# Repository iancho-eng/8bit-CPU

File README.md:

# 🖥️ 8-Bit CPU — Discrete Logic Computer

A fully functional 8-bit CPU designed in KiCAD and prototyped on breadboards, built from discrete TTL (74LS series) logic ICs with a microcoded control unit stored in parallel EEPROMs. The full design has now been carried from schematics through to custom, routed PCBs for every module.

> Inspired by Ben Eater's 8-bit computer series, this implementation extends the original design with custom modifications in components, organization, and debugging instrumentation.

---

## 📸 Overview

The processor implements a classic **von Neumann architecture** with a shared 8-bit data bus, fetch–decode–execute pipeline, and over **80 LEDs** for real-time visualization of control signals, bus traffic, and register contents.

---

## ✨ Features

- **Adjustable clock**: sub-Hz manual stepping up to ~100 kHz continuous operation
- **Manual single-step mode**: debounced pushbutton for step-through debugging
- **Microcoded control unit**: EEPROM-based microcode with up to 8 micro-steps per instruction
- **Rich LED instrumentation**: >80 LEDs tracing every register, bus line, and control signal
- **7-segment display output**: binary-to-decimal decoding via EEPROM lookup table
- **Signed/unsigned display modes**: selectable via mode control input
- **Program Mode / Run Mode**: front-panel DIP switches for manual memory programming

---

## 🏗️ Architecture

```
┌─────────────────────────────────────────────┐
│              Control Logic                  │
│           (EEPROM + Step Counter)           │
└────────────────────┬────────────────────────┘
                     │
              ┌──────▼───────┐
              │   8-bit BUS  │
              └──────┬───────┘
       ┌─────────────┼─────────────┐
       │             │             │
  ┌────▼────┐  ┌─────▼─────┐ ┌────▼────┐
  │   PC    │  │  Registers │ │   ALU   │
  │(HCT161) │  │ A / B / IR │ │(LS283×2)│
  └────┬────┘  └─────┬─────┘ └────┬────┘
       │             │             │
  ┌────▼────┐  ┌─────▼─────┐ ┌────▼────┐
  │   MAR   │  │    RAM     │ │ Output  │
  │         │  │ (74189 ×2) │ │Register │
  └─────────┘  └───────────┘ └─────────┘
```

### System Characteristics

| Property       | Value                                    |
| -------------- | ----------------------------------------- |
| Bus Width      | 8-bit shared data bus                    |
| Clock Speed    | Sub-Hz (manual) to ~100 kHz (continuous) |
| Supply Voltage | 5V DC regulated                          |
| RAM            | 128 bytes (74189 × 2)                    |
| Indicators     | >80 LEDs                                 |
| Logic Family   | TTL — 74LS / 74HCT series                |
| PCB Stack-up   | 2-layer (F.Cu / B.Cu), KiCad              |

---

## 🔩 PCB Design

Every module of the CPU has been fully migrated from breadboard schematic to a routed, 2-layer KiCad PCB. Each board is a standalone module that plugs into the shared 8-bit bus, keeping the system modular and easy to debug or re-spin individually.

### Register A

8-bit accumulator register (`pcb/Register_A/Register_A.kicad_pcb`) — dual 74HCT173 D-type registers cascaded for 8 bits, bus-isolated via 74HCT245 transceiver, with LED taps on every output bit.

### Register B

8-bit operand register (`pcb/Register_B/Register_B.kicad_pcb`) — same 74HCT173 + 74HCT245 architecture as Register A.

### ALU

Dual 74LS283 4-bit adders (`pcb/ALU/ALU.kicad_pcb`) cascaded for 8-bit arithmetic, with a 74LS86 XOR network for two's-complement subtraction and 74LS02/74LS08 gating for the carry/zero flag logic.

### RAM

128-byte static RAM (`pcb/RAM/RAM.kicad_pcb`) — dual 74189 RAM chips, 74LS157 address/data muxing, 74LS04 inversion correction, and an 8-position DIP switch bank for manual Program Mode entry.

### MAR + Instruction Register

Memory Address Register and Instruction Register combined on one board (`pcb/MAR_Instruction_Register/MAR_Instruction_Register.kicad_pcb`) — dual 74HCT173 registers with manual DIP-switch address entry; the IR splits into opcode (upper nibble, to control logic) and operand (lower nibble, to bus).

### Program Counter + Output Register

Combined PC and display output board (`pcb/Program_Counter_Output_Register/Program_Counter_Output_Register.kicad_pcb`) — 74HCT161 program counter, 74HCT273 output latch, EEPROM-based binary-to-7-segment lookup table, and 74LS76/74LS08 digit-multiplexing driving a 4-digit CA56-12CGWA display.

### Control Logic

Microcode sequencer (`pcb/Control_Logic/Control_Logic.kicad_pcb`) — dual 28C16 EEPROMs storing `(opcode + step + flags) → control signals`, a 74HCT161 step counter, and LED taps on every control line.

### Clock

Clock generator (`pcb/Clock/Clock.kicad_pcb`) — triple 555 timer setup (astable for continuous clocking, monostable for debounced single-step), trimmer-potentiometer frequency control, and a run/step mode switch.

---

## 🔧 Modules

### Clock Module

- 555 timer in **astable mode** for continuous operation
- Potentiometer-controlled frequency (sub-Hz to ~100 kHz)
- Debounced pushbutton (555 in monostable mode) for single-step debugging

### Register Modules (A, B, Instruction)

- Built from **74HCT173** 4-bit D-type registers (cascaded pairs for 8-bit)
- All registers bus-isolated via **74LS245** transceivers
- LED taps on all outputs for real-time binary visualization
- IR splits into **opcode (upper nibble)** → control logic and **operand (lower nibble)** → bus

### ALU

- Dual **74LS283** 4-bit adders cascaded for 8-bit arithmetic
- XOR gate network (74LS86) enables **two's complement subtraction** via SUB control line
- Supports: `ADD`, `SUB`, bitwise `AND` / `OR` / `NOT` / `XOR`
- **Carry Flag (CF)**: MSB carry-out
- **Zero Flag (ZF)**: NOR/AND gate detection of all-zero result

### RAM

- Two **74189** static RAMs → 128 bytes total
- **Program Mode**: DIP switches + debounced write button
- **Run Mode**: CPU owns the bus; DIP inputs ignored
- 74LS157 multiplexers handle address/data source selection
- Data inversion corrected with 74LS04 inverters

### Program Counter (PC)

- **74HCT161** 4-bit synchronous counter + **74HCT245** bus transceiver
- Control inputs: `Load` (jump), `Enable` (controlled increment), `Clear/Reset`
- Green LEDs on output lines for address visualization

### Output Module

- **74HC273** octal D-type latch captures 8-bit bus value
- **28C16 EEPROM** as binary-to-7-segment lookup table
- **555 timer** + 74LS76 JK flip-flops + 74ACT139 decoder for digit multiplexing
- **CA56-12CGWA** 4-digit 7-segment display array
- Supports signed and unsigned decimal display modes

### Control Logic

- Two **28C16 EEPROMs** store microcode: `(opcode + step + flags) → control signals`
- **74HCT161** step counter cycles through up to 8 micro-steps per instruction
- Zero and Carry flags feed back into EEPROM address lines for conditional branching (`JZ`, `JC`)
- All control lines LED-tapped for real-time instruction sequencing visibility

---

## 📋 Instruction Set

| Mnemonic | Operation                    |
| -------- | ----------------------------- |
| `LDA`    | Load A register from memory  |
| `STA`    | Store A register to memory   |
| `ADD`    | Add memory value to A        |
| `SUB`    | Subtract memory value from A |
| `JMP`    | Unconditional jump           |
| `JC`     | Jump if carry flag set       |
| `JZ`     | Jump if zero flag set        |
| `OUT`    | Output A register to display |
| `HLT`    | Halt execution               |

---

## 💾 Sample Program

```
LDA 14    ; Load value at address 14 into register A
ADD 15    ; Add value at address 15 to register A
OUT       ; Latch result to 7-segment display
HLT       ; Halt
```

**Expected behavior**: fetches two operands from addresses 14 and 15, sums them in the ALU, and displays the decimal result on the 7-segment display before halting.

---

## 🛠️ Tools & Resources

| Tool                   | Purpose                                                           |
| ----------------------- | ------------------------------------------------------------------ |
| **KiCAD**               | Schematic design & PCB layout                                     |
| **Arduino IDE**         | EEPROM programmer firmware                                        |
| **Arduino Nano**        | Custom EEPROM programmer (with shift registers)                   |
| **LucidChart**          | Block diagram representation                                      |
| **Ben Eater's Series**  | Architecture reference — [eater.net/8bit](https://eater.net/8bit) |

---

## ⚙️ Operating Instructions

1. Connect a regulated **5V DC** supply to the PCB stack
2. Set the mode switch to **Program Mode**
3. Use DIP switches to set address and data values; press **WRITE** to store each byte
4. Switch to **Run Mode**
5. Select **Manual** (single-step) or **Continuous** clock mode
6. Press **RESET** to clear the PC and registers
7. Start the clock and observe execution on LEDs and 7-segment displays

---

## ⚠️ Limitations

- **Memory**: 128 bytes total RAM
- **Speed**: ~100 kHz practical limit (bounded by 74LS propagation delays and board wiring)
- **Debugging**: Longer programs require careful micro-step tracing
- **EEPROM wear**: 28C16 devices have finite write cycles — re-flash microcode judiciously

---

## 🚧 Current Status

- [x] Breadboard prototype functional
- [x] All modules designed in KiCAD
- [x] Arduino Nano EEPROM programmer built and tested
- [x] Decoupling/bypass capacitors added throughout
- [x] PCB layout routing complete for all 8 modules
- [x] PCB prototype fabrication & testing
- [ ] Full-system bring-up on fabricated boards

---

## 📄 License

This project is open-source and available under the [MIT License](https://github.com/iancho-eng/8bit-CPU/blob/main/LICENSE).

---

## 🙏 Acknowledgements

This project draws heavy inspiration from **Ben Eater's 8-bit computer series**. His tutorials and schematics provided a foundational understanding of CPU architecture. This implementation adapts and extends the design with independent modifications, additional debugging instrumentation, and a complete migration from breadboard to custom PCBs.

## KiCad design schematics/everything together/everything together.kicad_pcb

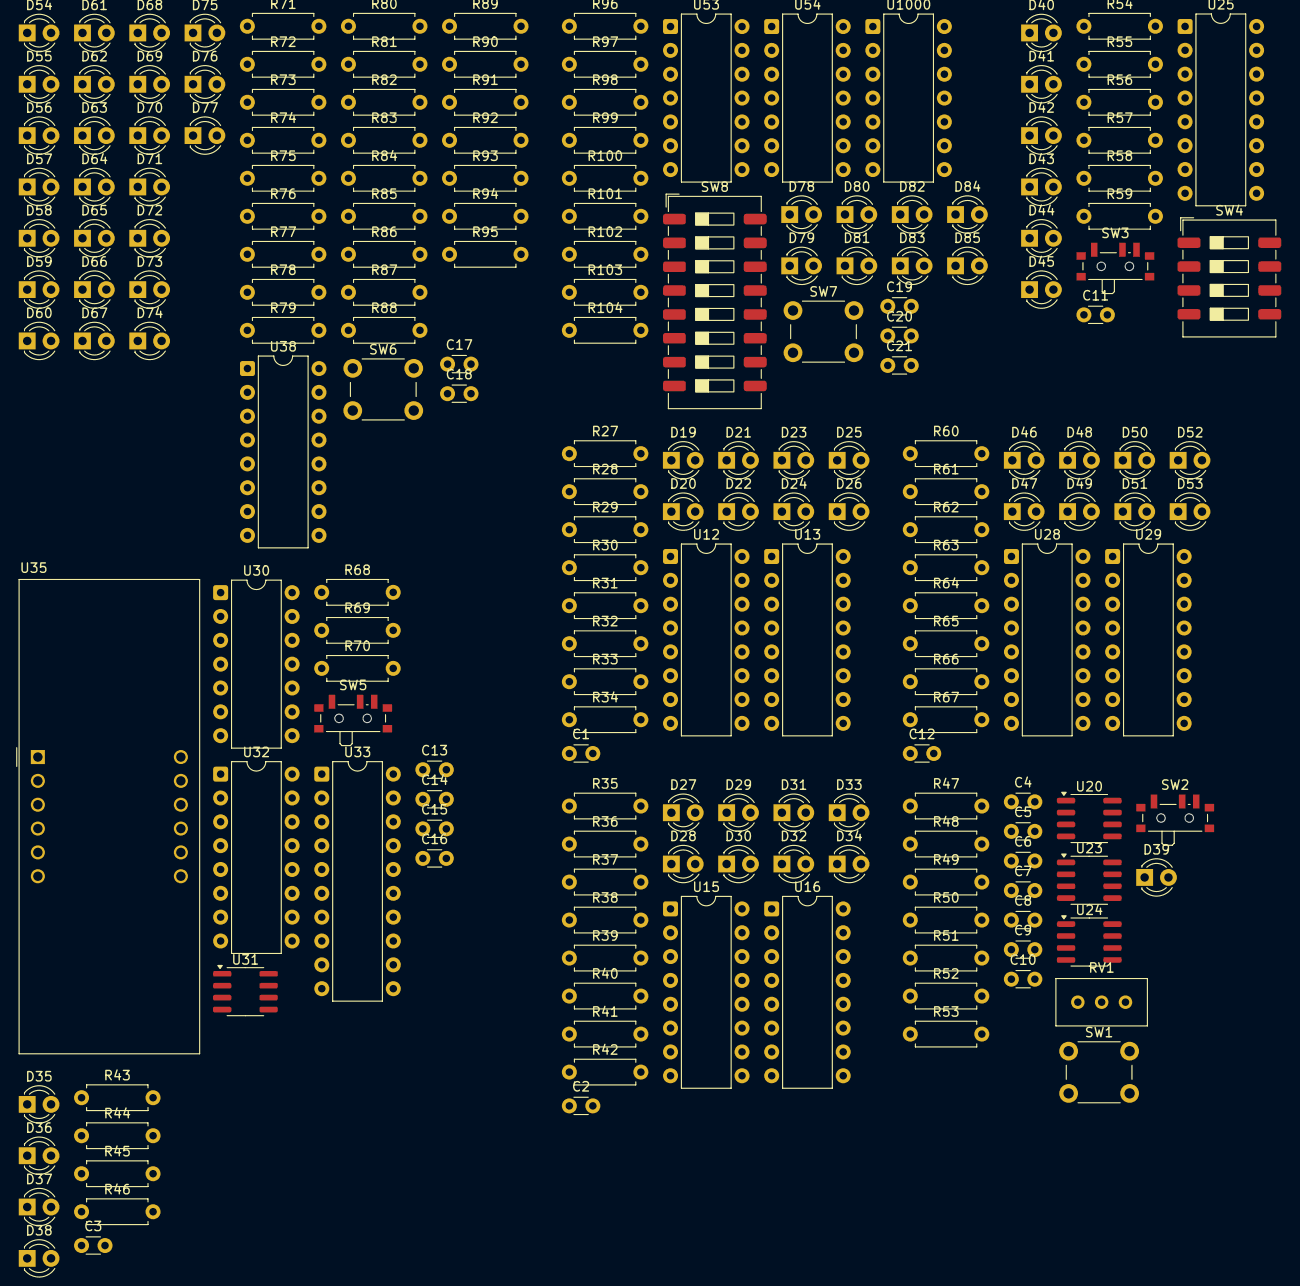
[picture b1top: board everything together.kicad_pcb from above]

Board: 2 copper layers, 194 parts (0 on the bottom side), 146 nets, no tracks yet.

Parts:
C1, C2, C3, C5, C9, C10, C12, C15, C16, C17, C18, C20, C21: 0.1uF; C_Disc_D3.0mm_W1.6mm_P2.50mm
C4, C6, C8, C13, C14, C19: 0.01uF; C_Disc_D3.0mm_W1.6mm_P2.50mm
C7: 1uF; C_Disc_D3.0mm_W1.6mm_P2.50mm
C11: C; C_Disc_D3.0mm_W1.6mm_P2.50mm
D19, D20, D21, D22, D23, D24, D25, D26, D27, D28, D29, D30, D31, D32, D33, D34, D41, D59, D60, D61, D78, D79, D80, D81, D82, D83, D84, D85: RED; LED_D3.0mm
D35, D36, D37, D38, D40, D54, D55, D56, D57, D58: GREEN; LED_D3.0mm
D39, D46, D47, D48, D49, D62, D63, D64, D65, D66, D67, D68, D69, D70, D71, D72, D73, D74, D75, D76, D77: BLUE; LED_D3.0mm
D42, D43, D44, D45, D50, D51, D52, D53: YELLOW; LED_D3.0mm
R27, R28, R29, R30, R31, R32, R33, R34, R35, R36, R37, R38, R39, R40, R41, R42, R43, R44, R45, R46, R51, R56, R57, R58, R59, R60, R61, R62, R63, R64, R65, R66, R67, R71, R72, R73, R74, R75, R77, R78, R79, R80, R81, R82, R83, R84, R85, R86, R87, R88, R89, R90, R91, R92, R93, R94, R95, R96, R97, R98, R99, R100, R101, R102, R103: 220; R_Axial_DIN0207_L6.3mm_D2.5mm_P7.62mm_Horizontal
R47, R49, R50, R52, R53, R54, R55, R76, R104: 1K; R_Axial_DIN0207_L6.3mm_D2.5mm_P7.62mm_Horizontal
R48: 1M; R_Axial_DIN0207_L6.3mm_D2.5mm_P7.62mm_Horizontal
R68: 10k; R_Axial_DIN0207_L6.3mm_D2.5mm_P7.62mm_Horizontal
R69: 100k; R_Axial_DIN0207_L6.3mm_D2.5mm_P7.62mm_Horizontal
R70: 1k; R_Axial_DIN0207_L6.3mm_D2.5mm_P7.62mm_Horizontal
RV1: 1M; Potentiometer_Bourns_3296W_Vertical
SW1, SW6, SW7: SW_Push; SW_PUSH_6mm
SW2, SW3, SW5: SW_SPDT; SW_SPDT_PCM12
SW4: SW_DIP_x04; SW_DIP_SPSTx04_Slide_9.78x12.34mm_W8.61mm_P2.54mm
SW8: SW_DIP_x08; SW_DIP_SPSTx08_Slide_9.78x22.5mm_W8.61mm_P2.54mm
U12, U13, U15, U16, U25, U28, U29: 74HCT173; DIP-16_W7.62mm
U20, U23, U24, U31: LM555xM; SOIC-8_3.9x4.9mm_P1.27mm
U30: 74LS08; DIP-14_W7.62mm
U32: 74LS76; DIP-16_W7.62mm
U33: 74HCT273; DIP-20_W7.62mm
U35: CA56-12CGKWA
U38: 74HCT138; DIP-16_W7.62mm
U53, U1000: 74HCT04; DIP-14_W7.62mm
U54: 7400; DIP-14_W7.62mm

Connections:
/ALU/A_0: D26.2 (A), U13.6 (Q3)
/ALU/A_1: D25.2 (A), U13.5 (Q2)
/ALU/A_2: D24.2 (A), U13.4 (Q1)
/ALU/A_3: D23.2 (A), U13.3 (Q0)
/ALU/A_4: D22.2 (A), U12.6 (Q3)
/ALU/A_5: D21.2 (A), U12.5 (Q2)
/ALU/A_6: D20.2 (A), U12.4 (Q1)
/ALU/A_7: D19.2 (A), U12.3 (Q0)
/ALU/BUS_0: U13.11 (D3), U16.11 (D3), U25.11 (D3), U29.11 (D3), U33.3 (D0)
/ALU/BUS_1: U13.12 (D2), U16.12 (D2), U25.12 (D2), U29.12 (D2), U33.4 (D1)
/ALU/BUS_2: U13.13 (D1), U16.13 (D1), U25.13 (D1), U29.13 (D1), U33.7 (D2)
/ALU/BUS_3: U13.14 (D0), U16.14 (D0), U25.14 (D0), U29.14 (D0), U33.8 (D3)
/ALU/BUS_4: U12.11 (D3), U15.11 (D3), U28.11 (D3), U33.13 (D4)
/ALU/BUS_5: U12.12 (D2), U15.12 (D2), U28.12 (D2), U33.14 (D5)
/ALU/BUS_6: U12.13 (D1), U15.13 (D1), U28.13 (D1), U33.17 (D6)
/ALU/BUS_7: U12.14 (D0), U15.14 (D0), U28.14 (D0), U33.18 (D7)
/ALU/B_0: D34.2 (A), U16.6 (Q3)
/ALU/B_1: D33.2 (A), U16.5 (Q2)
/ALU/B_2: D32.2 (A), U16.4 (Q1)
/ALU/B_3: D31.2 (A), U16.3 (Q0)
/ALU/B_4: D30.2 (A), U15.6 (Q3)
/ALU/B_5: D29.2 (A), U15.5 (Q2)
/ALU/B_6: D28.2 (A), U15.4 (Q1)
/ALU/B_7: D27.2 (A), U15.3 (Q0)
/ALU/CLK: C19.1, D39.2 (A), U12.7 (Cp), U13.7 (Cp), U15.7 (Cp), U16.7 (Cp), U25.7 (Cp), U28.7 (Cp), U29.7 (Cp), U30.2
/ALU/CLR: U12.15 (Mr), U13.15 (Mr), U15.15 (Mr), U16.15 (Mr), U25.15 (Mr), U28.15 (Mr), U29.15 (Mr)
/Control Logic/IR_4: D49.2 (A), U28.6 (Q3)
/Control Logic/IR_5: D48.2 (A), U28.5 (Q2)
/Control Logic/IR_6: D47.2 (A), U28.4 (Q1)
/Control Logic/IR_7: D46.2 (A), U28.3 (Q0)
/Control Logic/OI: D73.2 (A), U30.1
/Control Logic/RI: D64.2 (A), U54.1
/Control Logic/~AI: U12.9 (E1), U12.10 (E2), U13.9 (E1), U13.10 (E2)
/Control Logic/~BI: U15.9 (E1), U15.10 (E2), U16.9 (E1), U16.10 (E2)
/Control Logic/~II: U28.9 (E1), U28.10 (E2), U29.9 (E1), U29.10 (E2)
/Control Logic/~MI: U25.9 (E1), U25.10 (E2)
/Memory Address Register/Prog: D41.1 (K), SW3.1 (A)
GND: C1.2, C2.2, C3.2, C4.2, C5.2, C6.2, C7.2, C8.2, C9.2, C10.2, C11.2, C12.2, C13.2, C14.2, C15.2, C16.2, C17.2, C18.2, C20.2, C21.2, D59.1 (K), D60.1 (K), D61.1 (K), R27.2, R28.2, R29.2, R30.2, R31.2, R32.2, R33.2, R34.2, R35.2, R36.2, R37.2, R38.2, R39.2, R40.2, R41.2, R42.2, R43.1, R44.1, R45.1, R46.1, R51.2, R56.1, R57.1, R58.1, R59.1, R60.2, R61.2, R62.2, R63.2, R64.2, R65.2, R66.2, R67.2, R68.2, R76.2, R80.2, R81.2, R82.2, R83.2, R84.2, R85.2, R86.2, R87.2, R88.2, R89.2, R90.2, R91.2, R92.2, R93.2, R94.2, R95.2, R96.2, R97.2, R98.2, R99.2, R100.2, R101.2, R102.2, R103.2, R104.2, SW1.1, SW2.2 (B), SW3.2 (B), SW4.3, SW4.4, SW4.7, SW4.8, SW7.2, SW8.3, SW8.4, SW8.7, SW8.8, SW8.11, SW8.12, SW8.15, SW8.16, U12.1 (Oe1), U12.2 (Oe2), U12.8 (GND), U13.1 (Oe1), U13.2 (Oe2), U13.8 (GND), U15.1 (Oe1), U15.2 (Oe2), U15.8 (GND), U16.1 (Oe1), U16.2 (Oe2), U16.8 (GND), U20.1 (GND), U23.1 (GND), U24.1 (GND), U24.6 (THR), U25.1 (Oe1), U25.2 (Oe2), U25.8 (GND), U28.1 (Oe1), U28.2 (Oe2), U28.8 (GND), U29.1 (Oe1), U29.2 (Oe2), U29.8 (GND), U30.7 (GND), U31.1 (GND), U32.13 (GND), U33.10 (GND), U38.4 (~E0), U38.8 (GND), U53.7 (GND), U54.7 (GND), U1000.7 (GND)
unnamed: C19.2, R104.1, U54.2
unnamed: D19.1 (K), R27.1
unnamed: D20.1 (K), R28.1
unnamed: D21.1 (K), R29.1
unnamed: D22.1 (K), R30.1
unnamed: D23.1 (K), R31.1
unnamed: D24.1 (K), R32.1
unnamed: D25.1 (K), R33.1
unnamed: D26.1 (K), R34.1
unnamed: D27.1 (K), R35.1
unnamed: D28.1 (K), R36.1
unnamed: D29.1 (K), R37.1
unnamed: D30.1 (K), R38.1
unnamed: D31.1 (K), R39.1
unnamed: D32.1 (K), R40.1
unnamed: D33.1 (K), R41.1
unnamed: D34.1 (K), R42.1
unnamed: D35.1 (K), R43.2
unnamed: D36.1 (K), R44.2
unnamed: D37.1 (K), R45.2
unnamed: D38.1 (K), R46.2
unnamed: D39.1 (K), R51.1
unnamed: D40.2 (A), R54.2
unnamed: D40.1 (K), SW3.3 (C)
unnamed: D41.2 (A), R55.2
unnamed: D42.1 (K), R56.2
unnamed: D43.1 (K), R57.2
unnamed: D44.1 (K), R58.2
unnamed: D45.1 (K), R59.2
unnamed: D46.1 (K), R60.1
unnamed: D47.1 (K), R61.1
unnamed: D48.1 (K), R62.1
unnamed: D49.1 (K), R63.1
unnamed: D50.2 (A), U29.3 (Q0)
unnamed: D50.1 (K), R64.1
unnamed: D51.2 (A), U29.4 (Q1)
unnamed: D51.1 (K), R65.1
unnamed: D52.2 (A), U29.5 (Q2)
unnamed: D52.1 (K), R66.1
unnamed: D53.2 (A), U29.6 (Q3)
unnamed: D53.1 (K), R67.1
unnamed: D54.2 (A), R71.1
unnamed: D54.1 (K), U38.11 (~Y4)
unnamed: D55.2 (A), R72.1
unnamed: D55.1 (K), U38.12 (~Y3)
unnamed: D56.2 (A), R73.1
unnamed: D56.1 (K), U38.13 (~Y2)
unnamed: D57.2 (A), R74.1
unnamed: D57.1 (K), U38.14 (~Y1)
unnamed: D58.2 (A), R75.1
unnamed: D58.1 (K), U38.15 (~Y0)
unnamed: D59.2 (A), R77.1
unnamed: D60.2 (A), R78.1
unnamed: D61.2 (A), R79.1
unnamed: D62.1 (K), R80.1
unnamed: D63.1 (K), R81.1
unnamed: D64.1 (K), R82.1
unnamed: D65.1 (K), R83.1
unnamed: D66.1 (K), R84.1
unnamed: D67.1 (K), R85.1
unnamed: D68.1 (K), R86.1
unnamed: D69.1 (K), R87.1
unnamed: D70.1 (K), R88.1
unnamed: D71.1 (K), R89.1
unnamed: D72.1 (K), R90.1
unnamed: D73.1 (K), R91.1
unnamed: D74.1 (K), R92.1
unnamed: D75.1 (K), R93.1
unnamed: D76.1 (K), R94.1
unnamed: D77.1 (K), R95.1
unnamed: D78.2 (A), U53.2
unnamed: D78.1 (K), R96.1
unnamed: D79.2 (A), U53.4
unnamed: D79.1 (K), R97.1
unnamed: D80.2 (A), U53.6
unnamed: D80.1 (K), R98.1
unnamed: D81.2 (A), U53.8
unnamed: D81.1 (K), R99.1
unnamed: D82.2 (A), U53.10
unnamed: D82.1 (K), R100.1
unnamed: D83.2 (A), U53.12
unnamed: D83.1 (K), R101.1
unnamed: D84.2 (A), U1000.2
unnamed: D84.1 (K), R102.1
unnamed: D85.2 (A), U1000.4
unnamed: D85.1 (K), R103.1
unnamed: U32.1 (C), U32.10 (~Q)
unnamed: R79.2, U38.1 (A0)
unnamed: R78.2, U38.2 (A1)
unnamed: R77.2, U38.3 (A2)
unnamed: R50.1, RV1.2
unnamed: R76.1, SW6.2
unnamed: R52.2, SW2.1 (A), U24.2 (TR)
unnamed: R53.2, SW2.3 (C), U24.4 (R)
unnamed: R68.1, SW5.1 (A)
unnamed: C4.1, U20.5 (CV)
unnamed: C5.1, R48.2, U20.6 (THR), U20.7 (DIS)
unnamed: R47.2, SW1.2, U20.2 (TR)
unnamed: C6.1, U23.5 (CV)
unnamed: R49.2, R50.2, U23.7 (DIS)
unnamed: C7.1, RV1.3, U23.2 (TR), U23.6 (THR)
unnamed: C8.1, U24.5 (CV)
unnamed: C14.1, U31.5 (CV)
unnamed: R69.1, R70.2, U31.7 (DIS)
unnamed: U31.3 (Q), U32.6 (C)
unnamed: C13.1, R69.2, U31.2 (TR), U31.6 (THR)
unnamed: U30.3, U33.11 (Cp)
VCC: C1.1, C2.1, C3.1, C9.1, C10.1, C11.1, C12.1, C15.1, C16.1, C17.1, C18.1, C20.1, C21.1, R47.1, R48.1, R49.1, R52.1, R53.1, R54.1, R55.1, R70.1, R71.2, R72.2, R73.2, R74.2, R75.2, SW5.3 (C), SW6.1, U12.16 (VCC), U13.16 (VCC), U15.16 (VCC), U16.16 (VCC), U20.4 (R), U20.8 (VCC), U23.4 (R), U23.8 (VCC), U24.8 (VCC), U25.16 (VCC), U28.16 (VCC), U29.16 (VCC), U30.14 (VCC), U31.8 (VCC), U32.2 (~S), U32.3 (~R), U32.4 (J), U32.5 (VCC), U32.7 (~S), U32.8 (~R), U32.9 (J), U32.12 (K), U32.16 (K), U33.20 (VCC), U38.5 (~E1), U38.6 (E2), U38.16 (VCC), U53.14 (VCC), U54.14 (VCC), U1000.14 (VCC)

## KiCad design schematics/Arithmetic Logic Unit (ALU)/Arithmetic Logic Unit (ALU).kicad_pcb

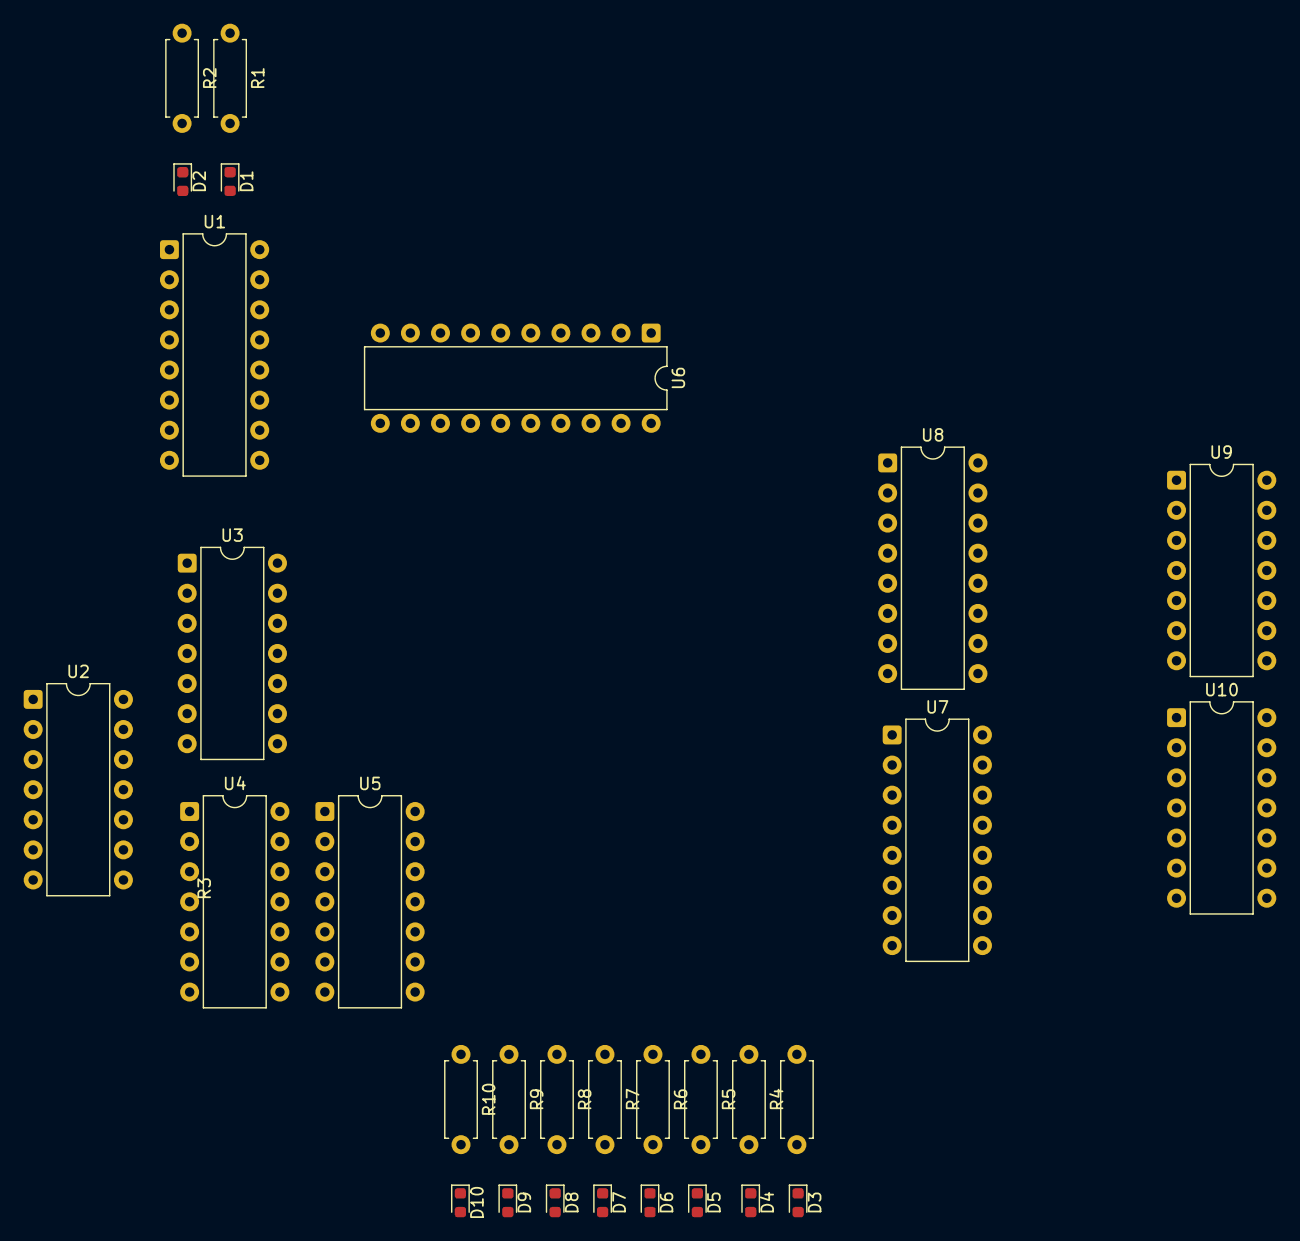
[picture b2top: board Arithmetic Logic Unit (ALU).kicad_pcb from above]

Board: 2 copper layers, 30 parts (0 on the bottom side), 41 nets, no tracks yet.

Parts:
D1, D2, D3, D4, D5, D6, D7, D8, D9, D10: RED; LED_0603_1608Metric
R1, R2, R3, R4, R5, R6, R7, R8, R9, R10: 220; R_Axial_DIN0207_L6.3mm_D2.5mm_P7.62mm_Horizontal
U1: 74HCT173; DIP-16_W7.62mm
U2, U3, U4: 74LS08; DIP-14_W7.62mm
U5: 74LS02; DIP-14_W7.62mm
U6: 74HCT245N; DIP-20_W7.62mm
U7, U8: 74LS283; DIP-16_W7.62mm
U9, U10: 74LS86; DIP-14_W7.62mm

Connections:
/CF: D1.2 (A), U1.3 (Q0)
/SU: U8.7 (C0), U9.1, U9.4, U9.9, U9.12, U10.1, U10.4, U10.9, U10.12
/ZF: D2.2 (A), U1.4 (Q1)
/~FI: U1.9 (E1), U1.10 (E2)
GND: R1.1, R2.1, R3.1, R4.1, R5.1, R6.1, R7.1, R8.1, R9.1, R10.1, U1.1 (Oe1), U1.2 (Oe2), U1.8 (GND), U6.10 (GND), U7.8 (GND), U8.8 (GND)
unnamed: D1.1 (K), R1.2
unnamed: D2.1 (K), R2.2
unnamed: D3.2 (A), U5.2, U6.2 (A0), U7.10 (S4)
unnamed: D3.1 (K), R3.2
unnamed: D4.2 (A), U5.3, U6.3 (A1), U7.13 (S3)
unnamed: D4.1 (K), R4.2
unnamed: D5.2 (A), U5.5, U6.4 (A2), U7.1 (S2)
unnamed: D5.1 (K), R5.2
unnamed: D6.2 (A), U5.6, U6.5 (A3), U7.4 (S1)
unnamed: D6.1 (K), R6.2
unnamed: D7.2 (A), U5.8, U6.6 (A4), U8.10 (S4)
unnamed: D7.1 (K), R7.2
unnamed: D8.2 (A), U5.9, U6.7 (A5), U8.13 (S3)
unnamed: D8.1 (K), R8.2
unnamed: D9.2 (A), U5.11, U6.8 (A6), U8.1 (S2)
unnamed: D9.1 (K), R9.2
unnamed: D10.2 (A), U5.12, U6.9 (A7), U8.4 (S1)
unnamed: D10.1 (K), R10.2
unnamed: U1.14 (D0), U7.9 (C4)
unnamed: U1.13 (D1), U2.3
unnamed: U2.1, U3.3
unnamed: U2.2, U4.3
unnamed: U3.1, U5.1
unnamed: U3.2, U5.4
unnamed: U4.1, U5.10
unnamed: U4.2, U5.13
unnamed: U7.6 (B1), U9.8
unnamed: U7.2 (B2), U9.6
unnamed: U7.15 (B3), U9.3
unnamed: U7.11 (B4), U10.11
unnamed: U7.7 (C0), U8.9 (C4)
unnamed: U8.6 (B1), U10.8
unnamed: U8.2 (B2), U10.6
unnamed: U8.15 (B3), U10.3
unnamed: U8.11 (B4), U9.11
VCC: U1.16 (VCC), U6.1 (DIR), U6.20 (VCC), U7.16 (VCC), U8.16 (VCC)

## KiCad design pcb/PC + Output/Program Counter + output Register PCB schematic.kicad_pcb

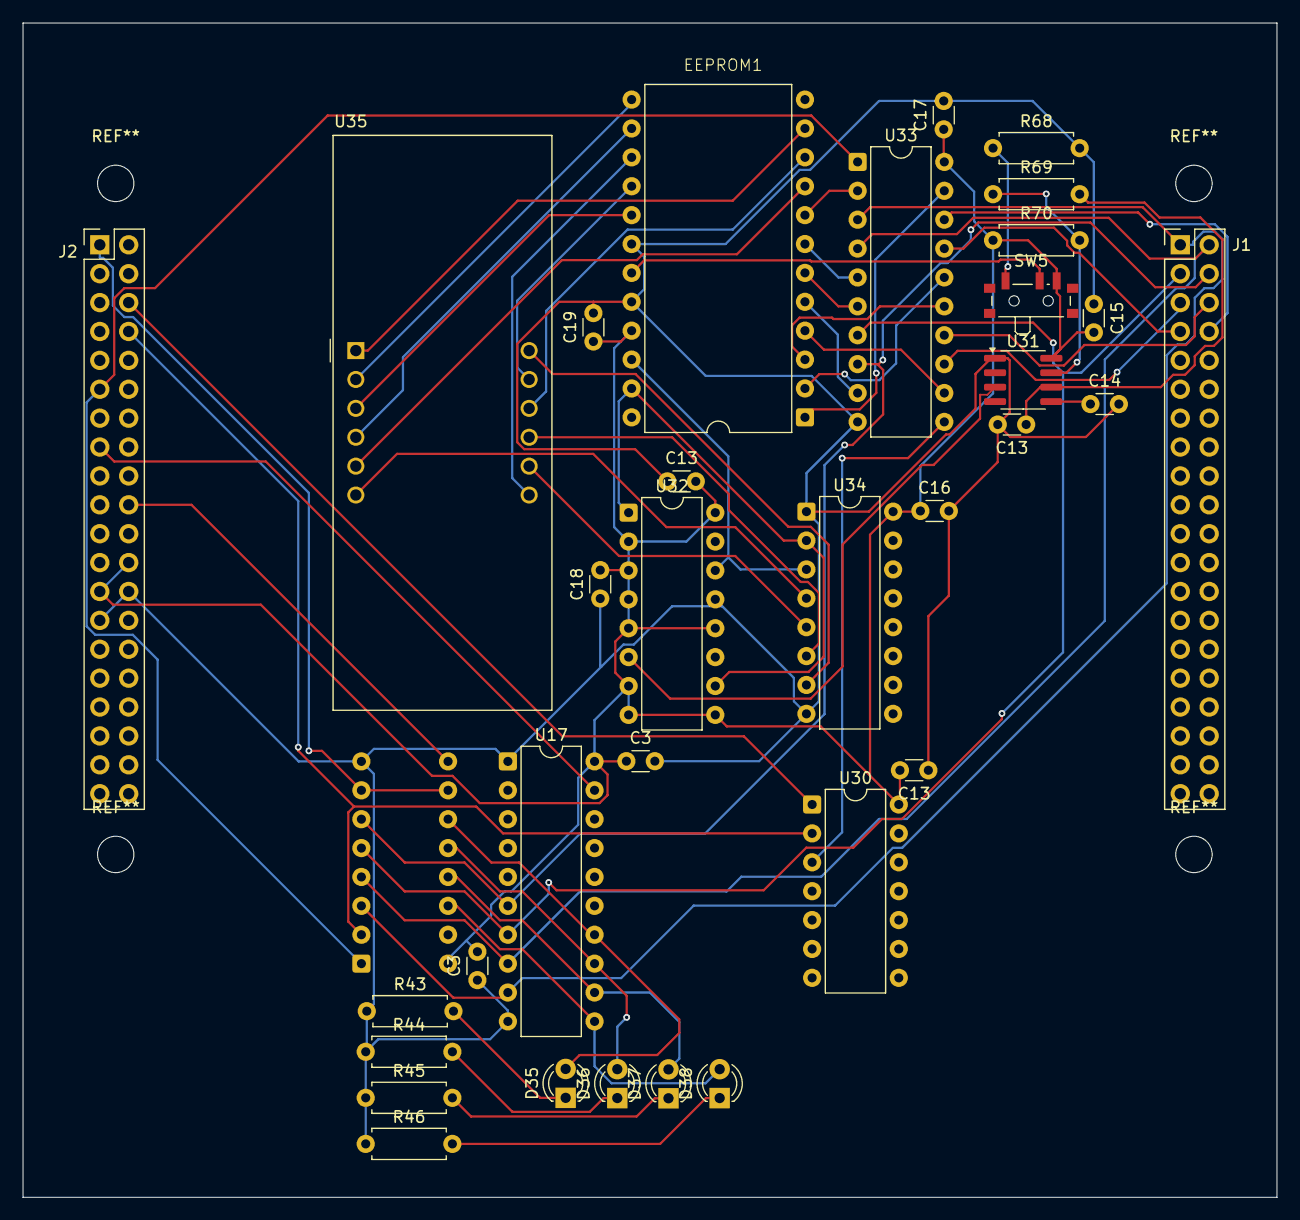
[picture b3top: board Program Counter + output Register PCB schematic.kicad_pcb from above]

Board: 2 copper layers, 110.2 x 103.2 mm, 34 parts (1 on the bottom side), 53 nets.

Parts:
C3, C3#2, C16, C17, C18, C19: 0.1uF; C_Disc_D3.0mm_W1.6mm_P2.50mm
C13, C13#2, C13#3, C14, C15: 0.01uF; C_Disc_D3.0mm_W1.6mm_P2.50mm
D35, D36, D37, D38: GREEN; LED_D3.0mm
EEPROM1: EEPROM
J1, J2: Conn_02x20_Odd_Even; PinHeader_2x20_P2.54mm_Vertical
R43, R44, R45, R46: 220; R_Axial_DIN0207_L6.3mm_D2.5mm_P7.62mm_Horizontal
R68: 10k; R_Axial_DIN0207_L6.3mm_D2.5mm_P7.62mm_Horizontal
R69: 100k; R_Axial_DIN0207_L6.3mm_D2.5mm_P7.62mm_Horizontal
R70: 1k; R_Axial_DIN0207_L6.3mm_D2.5mm_P7.62mm_Horizontal
SW5: SW_SPDT; SW_SPDT_PCM12
U17: 74HCT245N; DIP-20_W7.62mm
U18: 74HCT161D; DIP-16_W7.62mm
U30: 74LS08; DIP-14_W7.62mm
U31: LM555xM; SOIC-8_3.9x4.9mm_P1.27mm
U32: 74LS76; DIP-16_W7.62mm
U33: 74HCT273; DIP-20_W7.62mm
U34: 74HCT139D; DIP-16_W7.62mm
U35: CA56-12CGKWA

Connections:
/Output Register/BUS_0: J1.1, U17.9 (A7), U18.3 (D0), U33.3 (D0)
/Output Register/BUS_1: J1.2, U17.8 (A6), U18.4 (D1), U33.4 (D1)
/Output Register/BUS_2: J1.3, U17.7 (A5), U18.5 (D2), U33.7 (D2)
/Output Register/BUS_3: J1.4, U17.6 (A4), U18.6 (D3), U33.8 (D3)
/Output Register/BUS_4: J1.5, U33.13 (D4)
/Output Register/BUS_5: J1.6, U33.14 (D5)
/Output Register/BUS_6: J1.7, U33.17 (D6)
/Output Register/BUS_7: J1.8, U33.18 (D7)
/Output Register/CLK: J2.8, U18.2 (CP), U30.2
/Output Register/OI: J2.6, U30.1
/Output Register/~CLR: J2.11, U18.1 (~MR), U33.1 (~Mr)
/Program Counter Module/CE: J2.1, U18.7 (CEP), U18.10 (CET)
/Program Counter Module/~CO: J2.15, U17.19 (~OE)
/Program Counter Module/~J: J2.20, U18.9 (~PE)
GND: C3.2, C3#2.1, C13.1, C13#2.2, C13#3.1, C14.2, C15.1, C16.2, C17.2, C18.1, C19.2, EEPROM1.18 (~CE), EEPROM1.20 (~OE), J2.26, J2.27, R43.1, R44.1, R45.1, R46.1, R68.2, U17.1 (DIR), U17.10 (GND), U18.8 (GND), U30.7 (GND), U31.1 (GND), U32.13 (GND), U33.10 (GND), U34.1 (1~E), U34.8 (GND)
unnamed: D35.2 (A), U17.14 (B4), U18.11 (Q3)
unnamed: D35.1 (K), R43.2
unnamed: D36.2 (A), U17.13 (B5), U18.12 (Q2)
unnamed: D36.1 (K), R44.2
unnamed: D37.2 (A), U17.12 (B6), U18.13 (Q1)
unnamed: D37.1 (K), R45.2
unnamed: D38.2 (A), U17.11 (B7), U18.14 (Q0)
unnamed: D38.1 (K), R46.2
unnamed: EEPROM1.8 (A0), U33.2 (Q0)
unnamed: EEPROM1.7 (A1), U33.5 (Q1)
unnamed: EEPROM1.6 (A2), U33.6 (Q2)
unnamed: EEPROM1.5 (A3), U33.9 (Q3)
unnamed: EEPROM1.4 (A4), U33.12 (Q4)
unnamed: EEPROM1.3 (A5), U33.15 (Q5)
unnamed: EEPROM1.2 (A6), U33.16 (Q6)
unnamed: EEPROM1.1 (A7), U33.19 (Q7)
unnamed: EEPROM1.23 (A8), U32.1 (C), U32.10 (~Q), U34.2 (1A0)
unnamed: EEPROM1.22 (A9), U32.14 (~Q), U34.3 (1A1)
unnamed: EEPROM1.19 (A10), SW5.2 (B)
unnamed: EEPROM1.9 (D0), U35.5 (g)
unnamed: EEPROM1.10 (D1), U35.10 (f)
unnamed: EEPROM1.11 (D2), U35.1 (e)
unnamed: EEPROM1.13 (D3), U35.2 (d)
unnamed: EEPROM1.14 (D4), U35.4 (c)
unnamed: EEPROM1.15 (D5), U35.7 (b)
unnamed: EEPROM1.16 (D6), U35.11 (a)
unnamed: EEPROM1.17 (D7), U35.3 (DPX)
unnamed: R68.1, SW5.1 (A)
unnamed: C14.1, U31.5 (CV)
unnamed: R69.1, R70.2, U31.7 (DIS)
unnamed: U31.3 (Q), U32.6 (C)
unnamed: C13#2.1, R69.2, U31.2 (TR), U31.6 (THR)
unnamed: U30.3, U33.11 (Cp)
unnamed: U34.4 (1~Y0), U35.6 (CA4)
unnamed: U34.5 (1~Y1), U35.8 (CA3)
unnamed: U34.6 (1~Y2), U35.9 (CA2)
unnamed: U34.7 (1~Y3), U35.12 (CA1)
VCC: C3.1, C3#2.2, C13.2, C13#3.2, C15.2, C16.1, C17.1, C18.2, C19.1, EEPROM1.21 (~WE), J2.24, J2.25, R70.1, SW5.3 (C), U17.20 (VCC), U18.16 (VCC), U30.14 (VCC), U31.8 (VCC), U32.2 (~S), U32.3 (~R), U32.4 (J), U32.5 (VCC), U32.7 (~S), U32.8 (~R), U32.9 (J), U32.12 (K), U32.16 (K), U33.20 (VCC), U34.16 (VCC)

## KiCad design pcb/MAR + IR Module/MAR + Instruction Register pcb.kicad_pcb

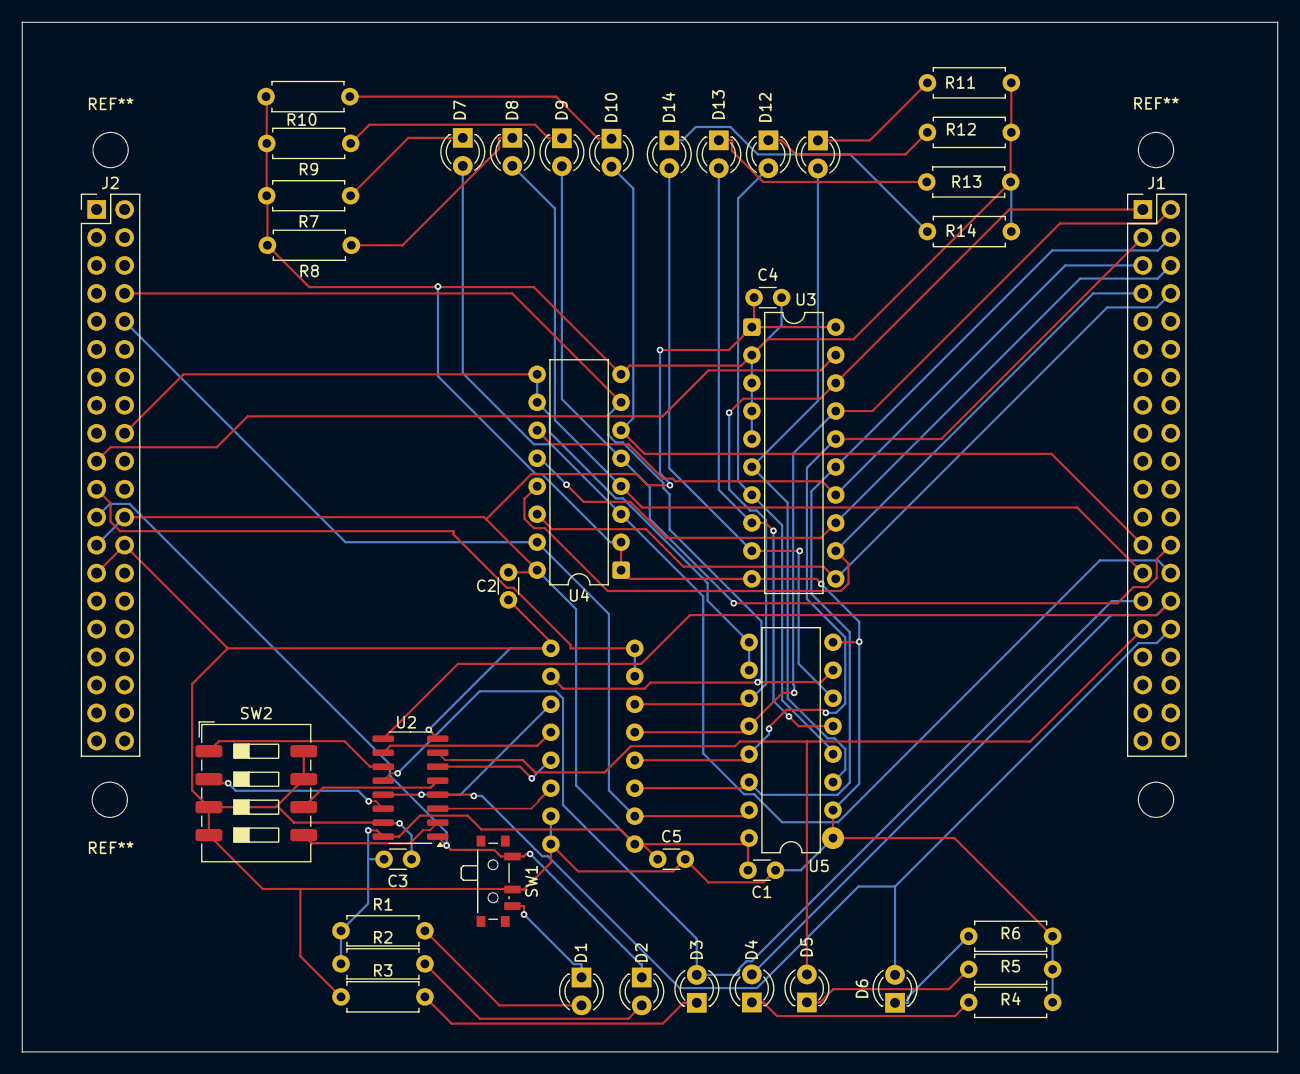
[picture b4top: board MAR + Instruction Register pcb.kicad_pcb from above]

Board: 2 copper layers, 114.0 x 93.5 mm, 42 parts (1 on the bottom side), 51 nets.

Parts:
C1, C2, C3, C4, C5: 0.1uF; C_Disc_D3.0mm_W1.6mm_P2.50mm
D1: GREEN; LED_D3.0mm
D2: RED; LED_D3.0mm
D3, D4, D5, D6, D11, D12, D13, D14: YELLOW; LED_D3.0mm
D7, D8, D9, D10: BLUE; LED_D3.0mm
J1, J2: Conn_02x20_Odd_Even; PinHeader_2x20_P2.54mm_Vertical
R1, R2: 1K; R_Axial_DIN0207_L6.3mm_D2.5mm_P7.62mm_Horizontal
R3, R4, R5, R6, R7, R8, R9, R10, R11, R12, R13, R14: 220; R_Axial_DIN0207_L6.3mm_D2.5mm_P7.62mm_Horizontal
SW1: SW_SPDT; SW_SPDT_PCM12
SW2: SW_DIP_x04; SW_DIP_SPSTx04_Slide_9.78x12.34mm_W8.61mm_P2.54mm
U1, U4, U5: 74HCT173; DIP-16_W7.62mm
U2: 74HCT157D; SOIC-16_3.9x9.9mm_P1.27mm
U3: 74HCT245N; DIP-20_W7.62mm

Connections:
/Instruction Register Module/BUS_0: J1.1, U1.11 (D3), U3.18 (B0), U5.11 (D3)
/Instruction Register Module/BUS_1: J1.2, U1.12 (D2), U3.17 (B1), U5.12 (D2)
/Instruction Register Module/BUS_2: J1.3, U1.13 (D1), U3.16 (B2), U5.13 (D1)
/Instruction Register Module/BUS_3: J1.4, U1.14 (D0), U3.15 (B3), U5.14 (D0)
/Instruction Register Module/BUS_4: J1.5, U3.14 (B4), U4.11 (D3)
/Instruction Register Module/BUS_5: J1.6, U3.13 (B5), U4.12 (D2)
/Instruction Register Module/BUS_6: J1.7, U3.12 (B6), U4.13 (D1)
/Instruction Register Module/BUS_7: J1.8, U3.11 (B7), U4.14 (D0)
/Instruction Register Module/CLK: J2.8, U1.7 (Cp), U4.7 (Cp), U5.7 (Cp)
/Instruction Register Module/CLR: J2.10, U1.15 (Mr), U4.15 (Mr), U5.15 (Mr)
/Instruction Register Module/IR_4: D10.2 (A), J1.25, U4.6 (Q3)
/Instruction Register Module/IR_5: D9.2 (A), J1.26, U4.5 (Q2)
/Instruction Register Module/IR_6: D8.2 (A), J1.27, U4.4 (Q1)
/Instruction Register Module/IR_7: D7.2 (A), J1.28, U4.3 (Q0)
/Instruction Register Module/~II: J2.18, U4.9 (E1), U4.10 (E2), U5.9 (E1), U5.10 (E2)
/Instruction Register Module/~IO: J2.19, U3.19 (~OE)
/Memory Address Register Module/A0: D3.2 (A), J1.29, U2.12 (4Y)
/Memory Address Register Module/A1: D4.2 (A), J1.30, U2.9 (3Y)
/Memory Address Register Module/A2: D5.2 (A), J1.31, U2.7 (2Y)
/Memory Address Register Module/A3: D6.2 (A), J1.32, U2.4 (1Y)
/Memory Address Register Module/PROG: D2.1 (K), J2.23, SW1.1 (A), U2.1 (S)
/Memory Address Register Module/~MI: J2.21, U1.9 (E1), U1.10 (E2)
GND: C1.2, C2.2, C3.2, C4.2, C5.2, J2.26, J2.27, R3.1, R4.1, R5.1, R6.1, R7.2, R8.2, R9.2, R10.2, R11.2, R12.2, R13.2, R14.2, SW1.2 (B), SW2.3, SW2.4, SW2.7, SW2.8, U1.1 (Oe1), U1.2 (Oe2), U1.8 (GND), U2.8 (GND), U2.15 (~E), U3.2 (A0), U3.3 (A1), U3.4 (A2), U3.5 (A3), U3.10 (GND), U4.1 (Oe1), U4.2 (Oe2), U4.8 (GND), U5.1 (Oe1), U5.2 (Oe2), U5.8 (GND)
unnamed: D1.2 (A), R1.2
unnamed: D1.1 (K), SW1.3 (C)
unnamed: D2.2 (A), R2.2
unnamed: D3.1 (K), R3.2
unnamed: D4.1 (K), R4.2
unnamed: D5.1 (K), R5.2
unnamed: D6.1 (K), R6.2
unnamed: D7.1 (K), R7.1
unnamed: D8.1 (K), R8.1
unnamed: D9.1 (K), R9.1
unnamed: D10.1 (K), R10.1
unnamed: D11.2 (A), U3.6 (A4), U5.3 (Q0)
unnamed: D11.1 (K), R11.1
unnamed: D12.2 (A), U3.7 (A5), U5.4 (Q1)
unnamed: D12.1 (K), R12.1
unnamed: D13.2 (A), U3.8 (A6), U5.5 (Q2)
unnamed: D13.1 (K), R13.1
unnamed: D14.2 (A), U3.9 (A7), U5.6 (Q3)
unnamed: D14.1 (K), R14.1
unnamed: U1.3 (Q0), U2.3 (1I1)
unnamed: U1.4 (Q1), U2.6 (2I1)
unnamed: U1.5 (Q2), U2.10 (3I1)
unnamed: U1.6 (Q3), U2.13 (4I1)
unnamed: SW2.5, U2.2 (1I0)
unnamed: SW2.6, U2.5 (2I0)
unnamed: SW2.1, U2.11 (3I0)
unnamed: SW2.2, U2.14 (4I0)
VCC: C1.1, C2.1, C3.1, C4.1, C5.1, J2.24, J2.25, R1.1, R2.1, U1.16 (VCC), U2.16 (VCC), U3.1 (DIR), U3.20 (VCC), U4.16 (VCC), U5.16 (VCC)
